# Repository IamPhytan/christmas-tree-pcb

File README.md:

# Christmas Tree PCB

> 'Tis the Season for Makers

For Christmas 2023, I designed and built these Christmas tree PCBs as gifts for my relatives.
I also used this project as an opportunity to learn PCB Art, ATtiny microcontroller programming, and SMD component soldering.
This project demonstrates how free and open-source software can be leveraged to realize hardware and software projects.

|                                  |                              |
| -------------------------------- | ---------------------------- |
|  |  |

## Instructions

To make your own Christmas tree PCB, a complete instruction guide is available in [`how-to.md`](how-to.md).

## License

This project is distributed under a [CERN-OHL-P-2.0](LICENSE) license.

## Acknowledgments

Thanks to @nadarbreicq for helping me choose the right family of ATtiny for my project needs.
Both Barbatronic and Heliox made good videos for anyone starting projects with ATtiny microcontrollers:

* @nadarbreicq - _Create flexible circuits with a vinyl cutter to make robots!_: https://youtu.be/GuyE88zjXyU
* @HelioxLab - _Program microcontrollers for your circuit boards! (ATtiny)_: https://youtu.be/KPtmi16cyaA

This project has been realized with the following stack of Free Open-Source Software. Thanks to the maintainers and contributors of these software tools:

* [FreeCAD](https://www.freecad.org) for the outline
* [Inkscape](https://inkscape.org) for the decoration and the art on the PCB
* [KiCAD](https://www.kicad.org) for the PCB design
* [PlatformIO](https://platformio.org) for programming

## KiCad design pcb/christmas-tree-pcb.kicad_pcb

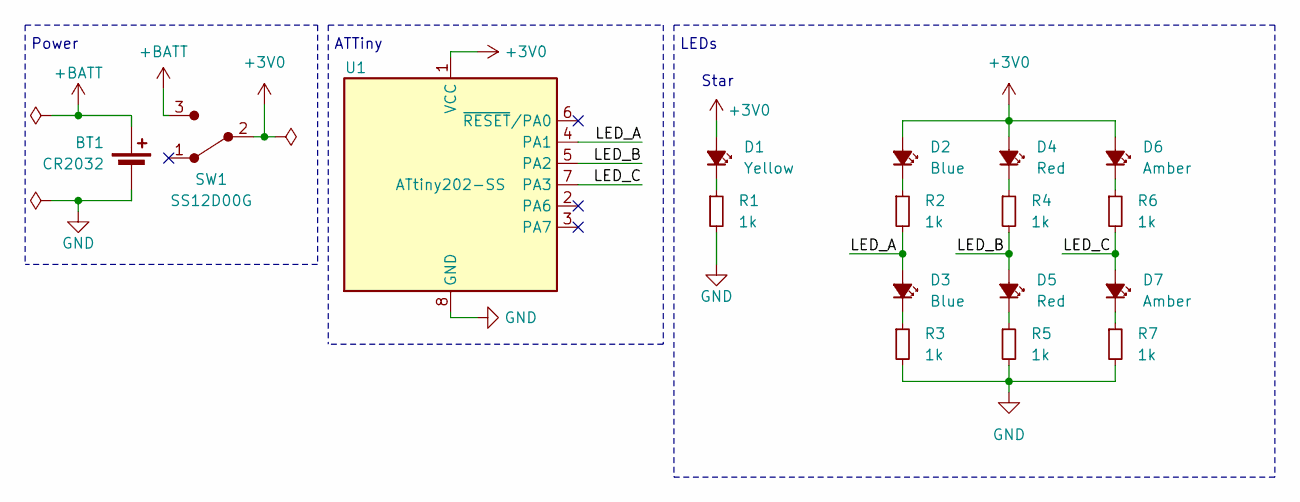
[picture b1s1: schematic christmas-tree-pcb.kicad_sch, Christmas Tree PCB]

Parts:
BT1: CR2032; BAT_BK-912
D1: Yellow; LED_1206_3216Metric_Pad1.42x1.75mm_HandSolder
D2, D3: Blue; LED_1206_3216Metric_Pad1.42x1.75mm_HandSolder
D4, D5: Red; LED_1206_3216Metric_Pad1.42x1.75mm_HandSolder
D6, D7: Amber; LED_1206_3216Metric_Pad1.42x1.75mm_HandSolder
R1, R2, R3, R4, R5, R6, R7: 1k; R_1206_3216Metric_Pad1.30x1.75mm_HandSolder
SW1: SS12D00G; SS-12D00-TH
U1: ATtiny202-SS; SOIC-8_3.9x4.9mm_P1.27mm

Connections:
+3V0: D1.2 (A), D2.2 (A), D4.2 (A), D6.2 (A), SW1.2 (B), U1.1 (VCC)
+BATT: BT1.+, SW1.3 (C)
/LED_A: D3.2 (A), R2.2, U1.4 (PA1)
/LED_B: D5.2 (A), R4.2, U1.5 (PA2)
/LED_C: D7.2 (A), R6.2, U1.7 (PA3)
GND: BT1.-, R1.2, R3.2, R5.2, R7.2, U1.8 (GND)
unnamed: D1.1 (K), R1.1
unnamed: D2.1 (K), R2.1
unnamed: D3.1 (K), R3.1
unnamed: D4.1 (K), R4.1
unnamed: D5.1 (K), R5.1
unnamed: D6.1 (K), R6.1
unnamed: D7.1 (K), R7.1

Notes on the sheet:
ATTiny
Power
LEDs
Star

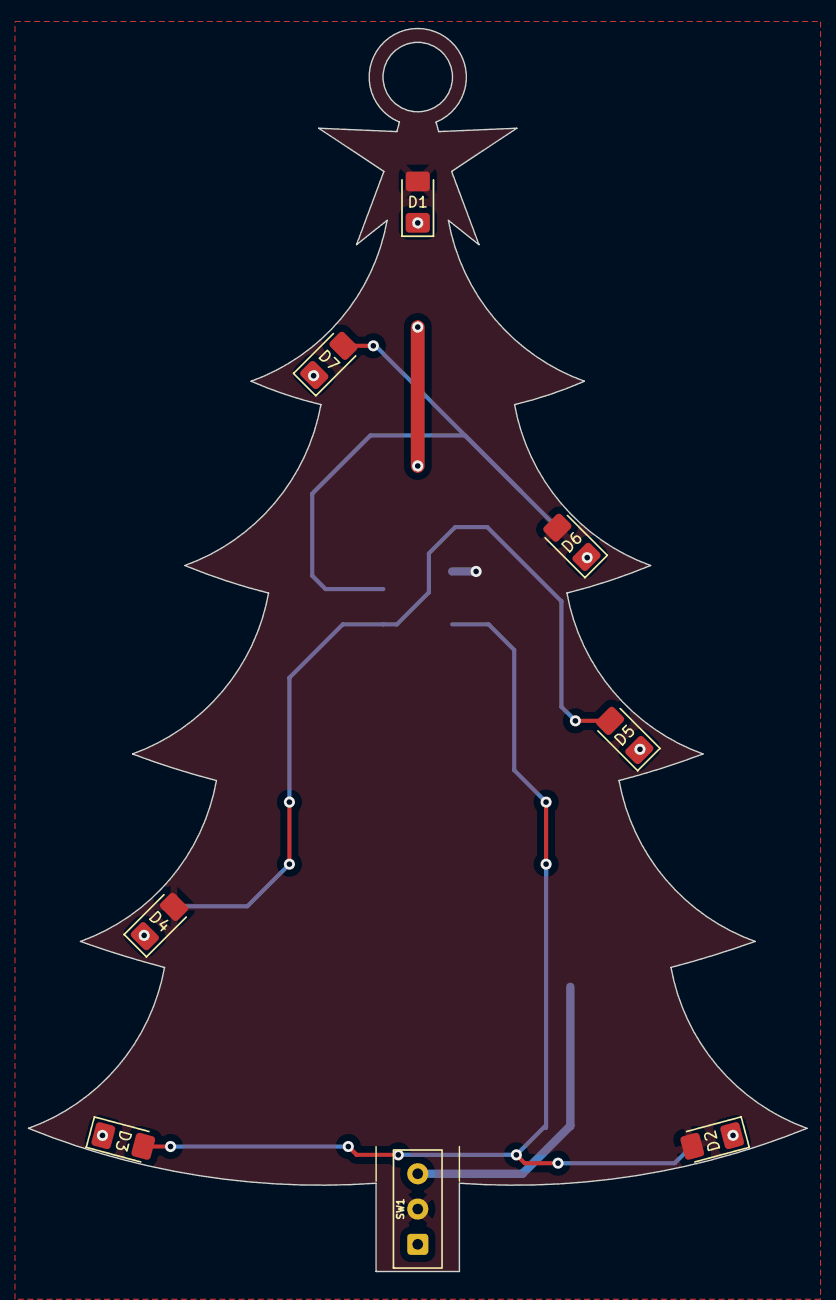
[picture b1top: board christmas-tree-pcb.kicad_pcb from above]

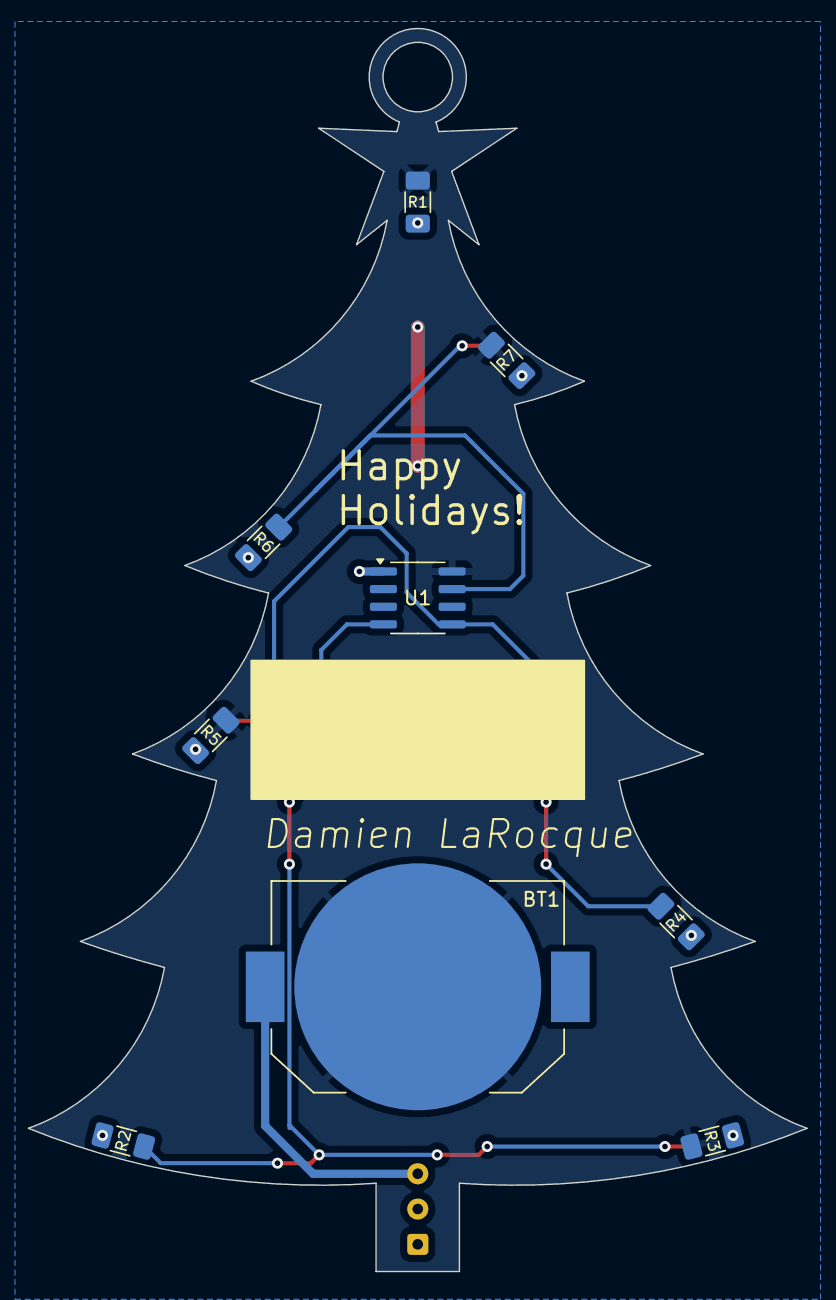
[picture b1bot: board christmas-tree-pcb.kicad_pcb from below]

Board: 2 copper layers, 56.1 x 89.5 mm, 17 parts (9 on the bottom side), 13 nets.

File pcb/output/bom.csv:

"Reference","Value","Footprint","Qty","Manufacturer","Manufacturer Ref","Vendor","Vendor Ref","Vendor URL"
"BT1","CR2032","christmas-tree:BAT_BK-912","1","MPD (Memory Protection Devices)","BK-912","DigiKey","BK-912-ND","https://www.digikey.com/en/products/detail/mpd-memory-protec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"
"D1","Yellow","LED_SMD:LED_1206_3216Metric_Pad1.42x1.75mm_HandSolder","1","Würth Elektronik","150120YS75000","DigiKey","732-4994-1-ND","https://www.digikey.com/en/products/detail/w%C3%BCrth-elektr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"
"D2,D3","Blue","LED_SMD:LED_1206_3216Metric_Pad1.42x1.75mm_HandSolder","2","Würth Elektronik","150120BS75000","DigiKey","732-4989-1-ND","https://www.digikey.com/en/products/detail/w%C3%BCrth-elektr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"
"D4,D5","Red","LED_SMD:LED_1206_3216Metric_Pad1.42x1.75mm_HandSolder","2","Würth Elektronik","150120SS75000","DigiKey","732-4992-1-ND","https://www.digikey.com/en/products/detail/w%C3%BCrth-elektr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"
"D6,D7","Amber","LED_SMD:LED_1206_3216Metric_Pad1.42x1.75mm_HandSolder","2","Würth Elektronik","150120AS75000","DigiKey","732-4988-1-ND","https://www.digikey.com/en/products/detail/w%C3%BCrth-elektr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"
"R1,R2,R3,R4,R5,R6,R7","1k","Resistor_SMD:R_1206_3216Metric_Pad1.30x1.75mm_HandSolder","7","YAGEO","RC1206FR-071KL","DigiKey","311-1.00KFRCT-ND","https://www.digikey.com/en/products/detail/yageo/RC1206FR-07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"
"SW1","SS12D00G","christmas-tree:SS-12D00-TH","1","N/A","SS12D00G","AliExpress","SS12D00","https://fr.aliexpress.com/item/4001207529493.html"
"U1","ATtiny202-SS","Package_SO:SOIC-8_3.9x4.9mm_P1.27mm","1","Microchip Technology","ATTINY202-SSFR","DigiKey","ATTINY202-SSFRCT-ND","https://www.digikey.com/en/products/detail/microchip-technol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"

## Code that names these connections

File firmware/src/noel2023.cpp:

#include <Arduino.h>

#define LED_A PIN_PA1
#define LED_B PIN_PA2
#define LED_C PIN_PA3

int randomSign(void);
int randomValue(void);
const int signs[2] = {-1, 1};

void setup() {
    pinMode(LED_A, OUTPUT);
    pinMode(LED_B, OUTPUT);
    pinMode(LED_C, OUTPUT);
}

void loop() {
    analogWrite(LED_A, randomValue());
    analogWrite(LED_B, randomValue());
    analogWrite(LED_C, randomValue());
    delay(random(300, 600));
}

int randomValue() {
    return 127 + randomSign() * random(80, 127);
}

int randomSign() {
    return signs[random(2)];
}

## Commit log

2024-12-23 Add PlatformIO project
2024-12-23 Start README
2025-01-09 Add PCB layout files; FreeCAD + Inkscape
2025-01-10 Add PCB component libraries
2025-01-10 WIP on PCB; tidy up the schematic
2025-01-10 Export BOM
2025-01-10 PCB layout; Comply with DRC
2025-01-10 WIP on documentation
2025-01-10 Add workflow to deploy files on GitHub Pages
2025-01-12 WIP on docs; add LICENSE
2025-01-13 WIP on docs; add list of components
2025-01-13 Remove workflow file
2025-01-13 Finish docs; Ship it
2025-01-14 Add PCB layout image
